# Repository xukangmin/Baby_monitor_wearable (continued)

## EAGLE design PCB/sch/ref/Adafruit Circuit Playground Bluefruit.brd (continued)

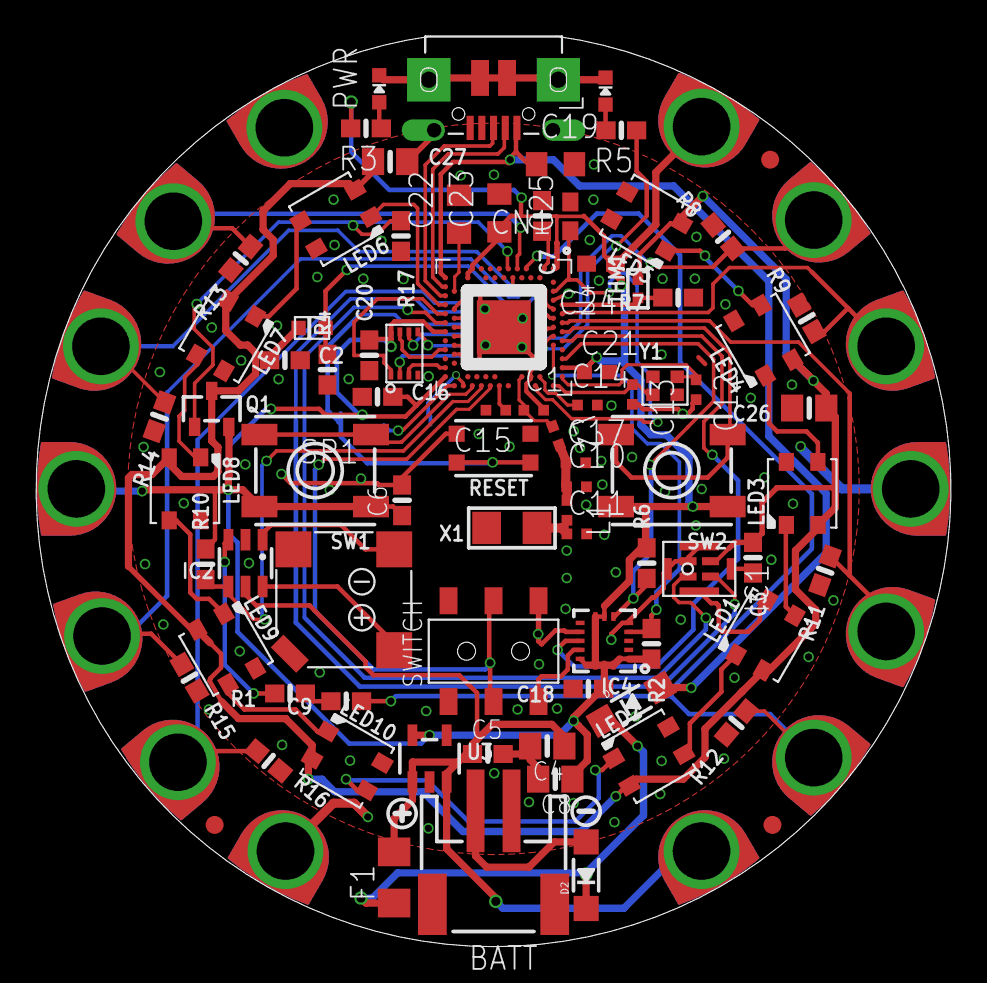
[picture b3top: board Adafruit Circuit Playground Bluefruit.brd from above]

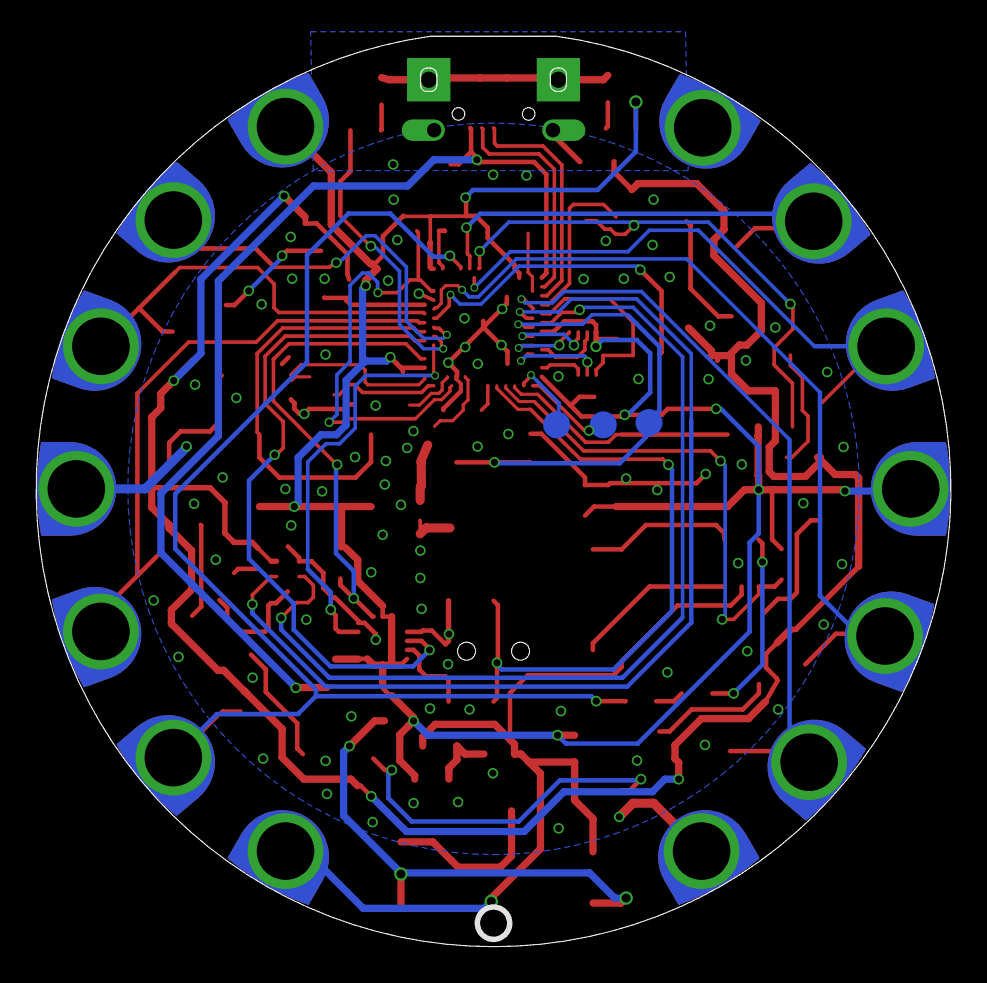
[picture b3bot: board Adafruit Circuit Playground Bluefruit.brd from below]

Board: 2 copper layers, 50.8 x 50.6 mm, 104 parts (5 on the bottom side), 65 nets.

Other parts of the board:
U$1: SYMBOL_MINUS
U$7: PCBFEAT-REV-040
U$16: CPLAY_BLUEFRUIT_BOT
U$35: SYMBOL_PLUS
U$44: CPLAY_BLUEFRUIT_TOP

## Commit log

2021-04-08 add android app.
2021-06-15 clean up
